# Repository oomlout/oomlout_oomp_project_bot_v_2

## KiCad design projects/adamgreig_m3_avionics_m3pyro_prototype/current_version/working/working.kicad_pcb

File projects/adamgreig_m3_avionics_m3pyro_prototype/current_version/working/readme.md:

# m3_avionics
 
## summary 
* id: adamgreig_m3_avionics_m3pyro_prototype
* user: adamgreig
* name: m3_avionics
* board: m3pyro_prototype
* repo: https://github.com/adamgreig/m3-avionics
* src_file_repo_kicad_pcb: m3pyro/firing_prototype/m3pyro_prototype.kicad_pcb
* src_file_repo_kicad_pcb_link: https://github.com/adamgreig/m3-avionics/tree/master/m3pyro/firing_prototype/m3pyro_prototype.kicad_pcb

* src_file_repo_sch: m3pyro/firing_prototype/m3pyro_prototype.sch
* src_file_repo_sch_link: https://github.com/adamgreig/m3-avionics/tree/master/m3pyro/firing_prototype/m3pyro_prototype.sch
* full details link: https://github.com/oomlout/oomlout_oomp_project_bot_v_2/tree/main/projects/adamgreig_m3_avionics_m3pyro_prototype/current_version/working  

## schematic  
  
[schematic (pdf)](working_schematic.pdf) 

## pcb  

[board (pdf)](working.pdf)  

## working_bom
| Id | Designator | Footprint | Quantity | Designation | Supplier and ref |  | None | 
| --- | --- | --- | --- | --- | --- | --- | --- | 
| 1 | L1 | XFL4020 | 1 | 2Âµ2 |  |  | [''] | 
| 2 | TP1 | TESTPAD | 1 | TESTPAD |  |  | [''] | 
| 3 | J1 | SIL-254P-02 | 1 | INPUT |  |  | [''] | 
| 4 | J2 | SIL-254P-02 | 1 | ENABLE |  |  | [''] | 
| 5 | J3 | SIL-254P-02 | 1 | OUTPUT |  |  | [''] | 
| 6 | IC1 | QFN-16-EP-TI | 1 | TPS62130 |  |  | [''] | 
| 7 | C1,C4 | 0603 | 2 | 10Âµ |  |  | [''] | 
| 8 | C2 | 0603 | 1 | 100n |  |  | [''] | 
| 9 | C3,R1,R2 | 0603 | 3 | DNP |  |  | [''] | 
| 10 | REF**,REF**,REF**,REF** | M3_MOUNT | 4 | M3_MOUNT |  |  | [''] | 

## bom_schematic
| Ref | Qnty | Value | Cmp name | Footprint | Description | Vendor | DNP | 
| --- | --- | --- | --- | --- | --- | --- | --- | 
| C1, C4 | 2 | 10Âµ | C | agg:0603 |  |  |  | 
| C2 | 1 | 100n | C | agg:0603 |  |  |  | 
| C3 | 1 | DNP | C | agg:0603 |  |  |  | 
| IC1 | 1 | TPS62130 | TPS62130 | agg:QFN-16-EP-TI |  |  |  | 
| J1 | 1 | INPUT | CONN_01x02 | agg:SIL-254P-02 |  |  |  | 
| J2 | 1 | ENABLE | CONN_01x02 | agg:SIL-254P-02 |  |  |  | 
| J3 | 1 | OUTPUT | CONN_01x02 | agg:SIL-254P-02 |  |  |  | 
| L1 | 1 | 2Âµ2 | L | agg:XFL4020 |  |  |  | 
| R1, R2 | 2 | DNP | R | agg:0603 |  |  |  | 
| TP1 | 1 | TESTPAD | TESTPAD | agg:TESTPAD |  |  |  |

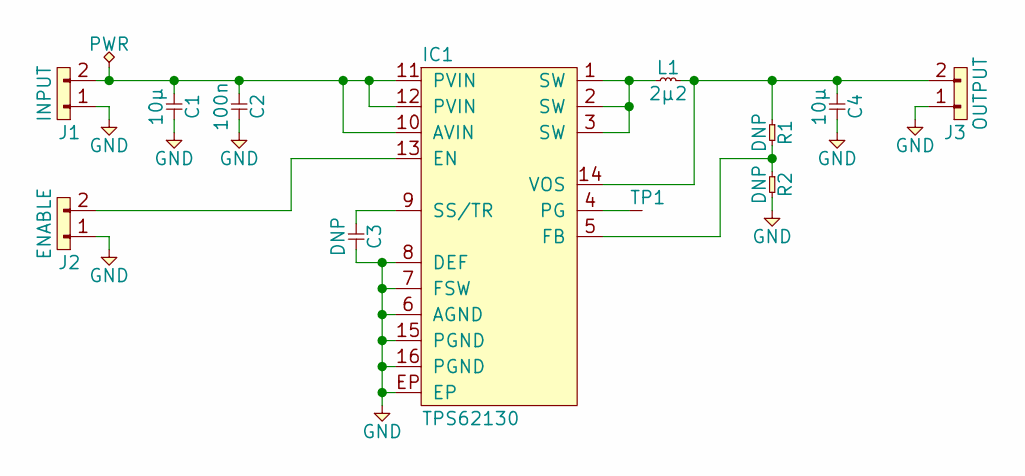
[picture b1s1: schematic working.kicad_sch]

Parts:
C1, C4: 10µ; 0603
C2: 100n; 0603
C3: DNP; 0603
IC1: TPS62130; QFN-16-EP-TI; Farnell 2361246
J1: INPUT; SIL-254P-02
J2: ENABLE; SIL-254P-02
J3: OUTPUT; SIL-254P-02
L1: 2µ2; XFL4020; Farnell 2289216
R1, R2: DNP; 0603
TP1: TESTPAD

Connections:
GND: C1.2, C2.2, C3.2, C4.2, IC1.6 (AGND), IC1.7 (FSW), IC1.8 (DEF), IC1.15 (PGND), IC1.16 (PGND), IC1.EP, J1.1, J2.1, J3.1, R2.2
unnamed: C1.1, C2.1, IC1.10 (AVIN), IC1.11 (PVIN), IC1.12 (PVIN), J1.2
unnamed: C3.1, IC1.9 (SS/TR)
unnamed: C4.1, IC1.14 (VOS), J3.2, L1.2, R1.1
unnamed: IC1.1 (SW), IC1.2 (SW), IC1.3 (SW), L1.1
unnamed: IC1.4 (PG), TP1.1
unnamed: IC1.5 (FB), R1.2, R2.1
unnamed: IC1.13 (EN), J2.2

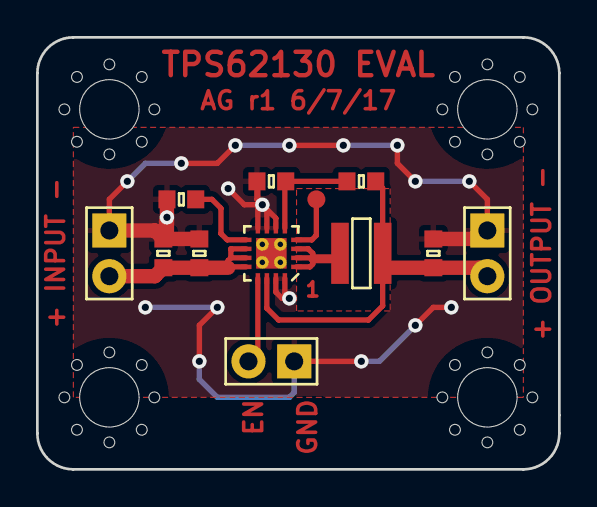
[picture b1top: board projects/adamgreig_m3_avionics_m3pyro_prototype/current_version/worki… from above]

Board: 2 copper layers, 29.0 x 24.0 mm, 12 parts (0 on the bottom side), 8 nets.

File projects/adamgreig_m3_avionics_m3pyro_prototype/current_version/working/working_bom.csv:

"Id";"Designator";"Footprint";"Quantity";"Designation";"Supplier and ref";
1;"L1";"XFL4020";1;"2µ2";;;
2;"TP1";"TESTPAD";1;"TESTPAD";;;
3;"J1";"SIL-254P-02";1;"INPUT";;;
4;"J2";"SIL-254P-02";1;"ENABLE";;;
5;"J3";"SIL-254P-02";1;"OUTPUT";;;
6;"IC1";"QFN-16-EP-TI";1;"TPS62130";;;
7;"C1,C4";"0603";2;"10µ";;;
8;"C2";"0603";1;"100n";;;
9;"C3,R1,R2";"0603";3;"DNP";;;
10;"REF**,REF**,REF**,REF**";"M3_MOUNT";4;"M3_MOUNT";;;

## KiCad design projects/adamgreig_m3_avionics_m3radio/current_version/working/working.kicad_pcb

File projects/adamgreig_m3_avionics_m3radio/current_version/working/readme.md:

# m3_avionics
 
## summary 
* id: adamgreig_m3_avionics_m3radio
* user: adamgreig
* name: m3_avionics
* board: m3radio
* repo: https://github.com/adamgreig/m3-avionics
* src_file_repo_kicad_pcb: m3radio/pcb_r2/m3radio.kicad_pcb
* src_file_repo_kicad_pcb_link: https://github.com/adamgreig/m3-avionics/tree/master/m3radio/pcb_r2/m3radio.kicad_pcb

* src_file_repo_sch: m3radio/gps-preamp/gps-preamp.sch
* src_file_repo_sch_link: https://github.com/adamgreig/m3-avionics/tree/master/m3radio/gps-preamp/gps-preamp.sch
* full details link: https://github.com/oomlout/oomlout_oomp_project_bot_v_2/tree/main/projects/adamgreig_m3_avionics_m3radio/current_version/working  

## schematic  
  
[schematic (pdf)](working_schematic.pdf) 

## pcb  

[board (pdf)](working.pdf)  

## working_bom
| Id | Designator | Footprint | Quantity | Designation | Supplier and ref |  | None | 
| --- | --- | --- | --- | --- | --- | --- | --- | 
| 1 | C103 | 0402 | 1 | 4u7 |  |  | [''] | 
| 2 | C104,C105,C107,C108,C109,C112,C113,C202,C1,C4,C9,C10 | 0402 | 12 | 100n |  |  | [''] | 
| 3 | C106,C2,C3,C7,C8 | 0402 | 5 | 1u |  |  | [''] | 
| 4 | C110,C111 | 0402 | 2 | 2u2 |  |  | [''] | 
| 5 | D101 | 0603-LED | 1 | RED |  |  | [''] | 
| 6 | D102 | 0603-LED | 1 | GRN |  |  | [''] | 
| 7 | IC101 | LQFP-64 | 1 | STM32F405RxTx |  |  | [''] | 
| 8 | IC102 | DFN-8-EP-MICROCHIP | 1 | MCP2562 |  |  | [''] | 
| 9 | IC201 | QFN-20-EP-SI | 1 | Si4461 |  |  | [''] | 
| 10 | J101 | TFML-110-02-L-D | 1 | WEST TOP |  |  | [''] | 
| 11 | J103 | TFML-110-02-L-D | 1 | EAST TOP |  |  | [''] | 
| 12 | R102,R103 | 0402 | 2 | 100 |  |  | [''] | 
| 13 | C201 | 0402 | 1 | 100p |  |  | [''] | 
| 14 | C203 | 0402 | 1 | 3p |  |  | [''] | 
| 15 | C204 | 0402 | 1 | 22p |  |  | [''] | 
| 16 | C205 | 0402 | 1 | 1p |  |  | [''] | 
| 17 | C206,C207 | 0402 | 2 | 5.6p |  |  | [''] | 
| 18 | L201 | 0603-L | 1 | 120nH |  |  | [''] | 
| 19 | L204 | 0603-L | 1 | 8.2nH |  |  | [''] | 
| 20 | C5,C11 | 0402 | 2 | 1n |  |  | [''] | 
| 21 | D1,D2 | 0402 | 2 | ESD_DIODE |  |  | [''] | 
| 22 | IC1 | DFN-6-EP-ONSEMI | 1 | NCP380 |  |  | [''] | 
| 23 | L1,L2,L3 | 0402-L | 3 | 91nH |  |  | [''] | 
| 24 | R1 | 0603 | 1 | 10 |  |  | [''] | 
| 25 | R2 | 0402 | 1 | 110k |  |  | [''] | 
| 26 | P101,P201 | U.FL-R-SMT-1 | 2 | COAX |  |  | [''] | 
| 27 | U1 | SC-70-5 | 1 | NCP4620 |  |  | [''] | 
| 28 | IC2 | SOT-23-5 | 1 | NC7SZ04 |  |  | [''] | 
| 29 | IC3 | MSOP-10 | 1 | CS2100-CP |  |  | [''] | 
| 30 | IC4 | DFN-10-SL18860DC | 1 | SL18860DC |  |  | [''] | 
| 31 | IC5 | MAX-M8Q | 1 | MAX_M8Q |  |  | [''] | 
| 32 | IC6 | SC-70-6 | 1 | SN74LVC1G0832 |  |  | [''] | 
| 33 | R3 | 0402 | 1 | 1M |  |  | [''] | 
| 34 | Y1 | TG-5006CG | 1 | TCXO |  |  | [''] | 
| 35 | C12 | 0402 | 1 | 220p |  |  | [''] | 
| 36 | L202 | 0402 | 1 | 20nH |  |  | [''] | 
| 37 | L203 | 0402 | 1 | 24nH |  |  | [''] | 
| 38 | L205 | 0402 | 1 | 6.8nH |  |  | [''] | 
| 39 | R4,R5 | 0402 | 2 | 10k |  |  | [''] | 
| 40 | C13 | 0402 | 1 | 2.2u |  |  | [''] | 
| 41 | J102 | SFML-110-02-L-D-LC | 1 | WEST BOT |  |  | [''] | 
| 42 | J104 | SFML-110-02-L-D-LC | 1 | EAST BOT |  |  | [''] | 

## bom_schematic
| Ref | Qnty | Value | Cmp name | Footprint | Description | Vendor | DNP | 
| --- | --- | --- | --- | --- | --- | --- | --- | 
| C1, C4, C9, C10, C104, C105, C107, C108, C109, C112, C113 | 11 | 100n | C | agg:0402 |  |  |  | 
| C2, C3, C7, C8, C106 | 5 | 1u | C | agg:0402 |  |  |  | 
| C5, C11 | 2 | 1n | C | agg:0402 |  |  |  | 
| C103 | 1 | 4u7 | C | agg:0402 |  |  |  | 
| C110, C111 | 2 | 2u2 | C | agg:0402 |  |  |  | 
| D1 | 1 | ESD_DIODE | ESD_DIODE | agg:0402 |  |  |  | 
| D101 | 1 | RED | LED | agg:0603-LED |  |  |  | 
| D102 | 1 | GRN | LED | agg:0603-LED |  |  |  | 
| IC1 | 1 | NCP380 | NCP380 | agg:DFN-6-EP-ONSEMI |  |  |  | 
| IC2 | 1 | NC7SZ04 | NC7SZ04 | agg:SOT-23-5 |  |  |  | 
| IC3 | 1 | CS2100-CP | CS2100-CP | agg:MSOP-10 |  |  |  | 
| IC4 | 1 | SL18860DC | SL18860DC | agg:DFN-10-SL18860DC |  |  |  | 
| IC5 | 1 | MAX_M8Q | MAX_M8Q | agg:MAX-M8Q |  |  |  | 
| IC6 | 1 | SN74LVC1G0832 | SN74LVC1G0832 | agg:SC-70-6 |  |  |  | 
| IC101 | 1 | STM32F405RxTx | STM32F405RxTx | agg:LQFP-64 |  |  |  | 
| IC102 | 1 | MCP2562 | MCP2562 | agg:DFN-8-EP-MICROCHIP |  |  |  | 
| J101 | 1 | WEST TOP | CONN_02x10 | agg:TFML-110-02-L-D |  |  |  | 
| J102 | 1 | WEST BOT | CONN_02x10 | agg:SFML-110-02-L-D-LC |  |  |  | 
| J103 | 1 | EAST TOP | CONN_02x10 | agg:TFML-110-02-L-D |  |  |  | 
| J104 | 1 | EAST BOT | CONN_02x10 | agg:SFML-110-02-L-D-LC |  |  |  | 
| L1, L2, L3 | 3 | 91nH | L | agg:0402-L |  |  |  | 
| P101 | 1 | COAX | COAX | M3radio:U.FL-R-SMT-1 |  |  |  | 
| R1 | 1 | 10 | R | agg:0603 |  |  |  | 
| R2 | 1 | 110k | R | agg:0402 |  |  |  | 
| R3 | 1 | 1M | R | agg:0402 |  |  |  | 
| R102, R103 | 2 | 100 | R | agg:0402 |  |  |  | 
| U1 | 1 | NCP4620 | NCP4620 | agg:SC-70-5 |  |  |  | 
| Y1 | 1 | TCXO | TCXO | agg:TG-5006CG |  |  |  |

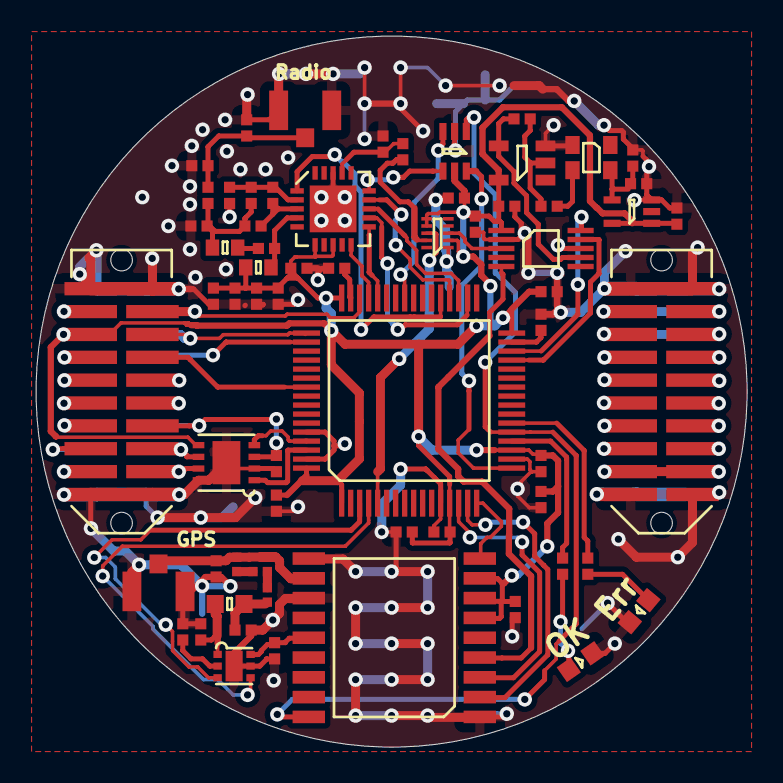
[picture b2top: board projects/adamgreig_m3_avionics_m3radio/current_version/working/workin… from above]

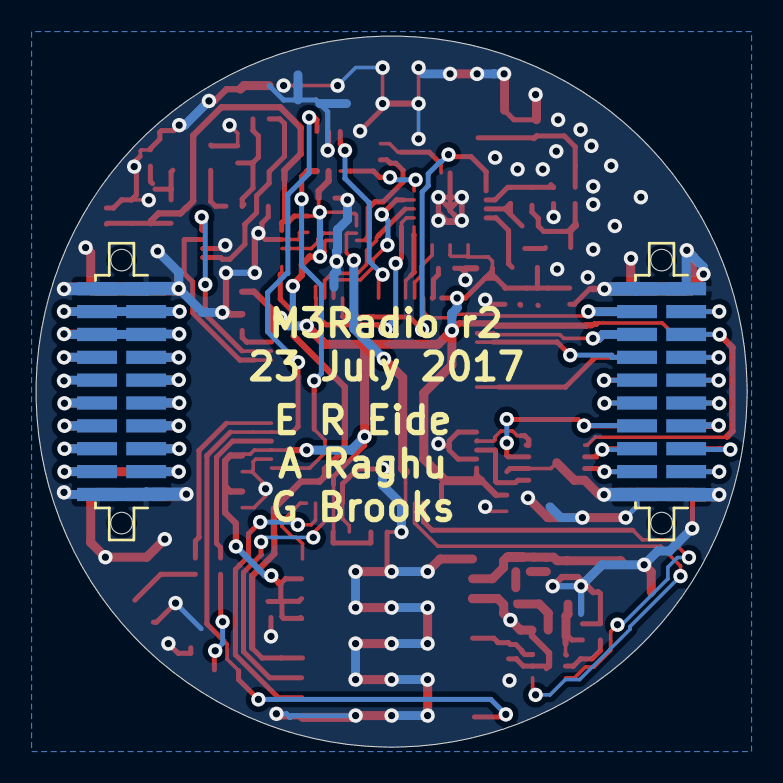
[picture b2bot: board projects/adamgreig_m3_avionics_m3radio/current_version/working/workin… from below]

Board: 2 copper layers, 39.5 x 39.5 mm, 66 parts (2 on the bottom side), 78 nets.

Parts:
C1, C4, C9, C10, C104, C105, C107, C108, C109, C112, C113, C202: 100n; 0402
C2, C3, C7, C8, C106: 1u; 0402
C5, C11: 1n; 0402
C12: 220p; 0402
C13: 2.2u; 0402
C103: 4u7; 0402
C110, C111: 2u2; 0402
C201: 100p; 0402
C203: 3p; 0402
C204: 22p; 0402
C205: 1p; 0402
C206, C207: 5.6p; 0402
D1, D2: ESD_DIODE; 0402
D101: RED; 0603-LED
D102: GRN; 0603-LED
IC1: NCP380; DFN-6-EP-ONSEMI
IC2: NC7SZ04; SOT-23-5
IC3: CS2100-CP; MSOP-10
IC4: SL18860DC; DFN-10-SL18860DC
IC5: MAX_M8Q; MAX-M8Q
IC6: SN74LVC1G0832; SC-70-6
IC101: STM32F405RxTx; LQFP-64
IC102: MCP2562; DFN-8-EP-MICROCHIP
IC201: Si4461; QFN-20-EP-SI
J101: WEST TOP; TFML-110-02-L-D
J102: WEST BOT; SFML-110-02-L-D-LC
J103: EAST TOP; TFML-110-02-L-D
J104: EAST BOT; SFML-110-02-L-D-LC
L1, L2, L3: 91nH; 0402-L
L201: 120nH; 0603-L
L202: 20nH; 0402
L203: 24nH; 0402
L204: 8.2nH; 0603-L
L205: 6.8nH; 0402
P101, P201: COAX; U.FL-R-SMT-1
R1: 10; 0603
R2: 110k; 0402
R3: 1M; 0402
R4, R5: 10k; 0402
R102, R103: 100; 0402
U1: NCP4620; SC-70-5
Y1: TCXO; TG-5006CG

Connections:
1v8: C4.1, C8.2, U1.4, Y1.4
3v3: C7.2, C9.1, C10.1, C11.2, C12.1, C13.1, C103.2, C104.2, C105.2, C106.2, C107.2, C108.2, C109.2, C113.1, C201.1, C202.1, IC2.5, IC3.1, IC4.2, IC4.6, IC4.7, IC5.6, IC5.7, IC5.8, IC6.5, IC101.1, IC101.13, IC101.19, IC101.32, IC101.48, IC101.64, IC102.5, IC201.6, IC201.8, J101.5, J102.5, L201.1, U1.1, U1.5
/3v3_AUX1: J101.13, J102.13
/3v3_AUX2: J101.15, J102.15
/3v3_DL: J101.11, J102.11
/3v3_FC: J101.7, J102.7
/3v3_IMU: J101.3, J102.3
/3v3_PYRO: J101.9, J102.9
/5v_AUX1: J103.11, J104.11
/5v_AUX2: J103.13, J104.13
/5v_CAM: J103.15, J104.15
/5v_CAN: C112.1, IC102.3, J101.14, J102.14
/5v_IMU: J103.9, J104.9
/5v_RADIO: J103.7, J104.7
/ANT_~EN: IC1.4, IC101.4
/ANT_~FLAG: IC1.3, IC101.3
/CAN+: IC102.7, J101.18, J102.18
/CAN-: IC102.6, J101.16, J102.16
/CAN_RXD: IC101.61, IC102.4
/CAN_TXD: IC101.62, IC102.1
/CHARGE: J103.17, J103.18, J104.17, J104.18
/GPS_PPS: IC5.18, IC6.1, IC101.21
/GPS_RESET_N: IC5.9, IC101.16
/GPS_RX: IC5.3, IC101.14
/GPS_TIM1: IC3.5, IC5.4
/GPS_TX: IC5.2, IC101.15
/JTCK: IC101.49, J101.6, J102.6
/JTDI: IC101.50, J102.8
/JTDO: IC101.55, J101.8
/JTDR: J101.10, J102.10
/JTMS: IC101.46, J101.4, J102.4
/LED_GRN: IC101.20, R103.1
/LED_RED: IC101.22, R102.1
/PLL_SCL: IC3.9, IC101.29
/PLL_SDA: IC3.10, IC101.30
/PWR: J103.16, J104.16
/PYRO1: J103.8, J104.8
/PYRO2: J103.10, J104.10
/PYRO3: J103.12, J104.12
/PYRO4: J103.14, J104.14
/PYRO_SI: J103.5, J103.6, J104.5, J104.6
/PYRO_SO: J103.3, J103.4, J104.3, J104.4
/RSVD1: J101.12, J102.12
/RSVD2: J101.17, J102.17
/Radio/RXn: C205.1, IC201.3, L202.1
/Radio/RXp: C203.1, IC201.2, L202.2, L203.1
/Radio/Radio_nSEL: IC6.4, IC201.15
/Radio/TX_pin: C204.1, IC201.4, L201.2
/Radio_CLK: IC4.9, R4.1
/Radio_GATE: IC6.3, IC101.41
/Radio_GPIO1: IC101.45, IC201.10
/Radio_SCLK: IC101.34, IC201.12
/Radio_SDI: IC101.36, IC201.14
/Radio_SDN: IC101.37, IC201.1
/Radio_SDO: IC101.35, IC201.13
/Radio_nIRQ: IC101.44, IC201.11
/Radio_nSEL: IC6.6, IC101.17
/STM_HSE: IC4.8, IC101.5
GND: C1.1, C2.2, C3.1, C4.2, C7.1, C8.1, C9.2, C10.2, C11.1, C12.2, C13.2, C103.1, C104.1, C105.1, C106.1, C107.1, C108.1, C109.1, C110.2, C111.2, C112.2, C113.2, C201.2, C202.2, C203.2, C206.2, C207.2, D1.2, D2.2, D101.1, D102.1, IC1.5, IC1.EP, IC2.3, IC3.2, IC3.8, IC4.1, IC5.1, IC5.10, IC5.12, IC6.2, IC101.12, IC101.18, IC101.60, IC101.63, IC102.2, IC102.8, IC102.EP, IC201.18, IC201.EP, J101.1, J101.2, J101.19, J101.20, J102.1, J102.2, J102.19, J102.20, J103.1, J103.2, J103.19, J103.20, J104.1, J104.2, J104.19, J104.20, P101.2, P201.2, R2.1, R5.2, U1.3, Y1.2
unnamed: C1.2, L3.1, R1.2
unnamed: C2.1, IC1.6, IC5.14
unnamed: C3.2, IC1.1, R1.1
unnamed: C5.1, IC2.2, R3.1
unnamed: C5.2, Y1.3
unnamed: C110.1, IC101.47
unnamed: C111.1, IC101.31
unnamed: C204.2, L204.1
unnamed: C205.2, C206.1, L203.2, L204.2, L205.1
unnamed: C207.1, D2.1, L205.2, P201.1
unnamed: D1.1, IC5.11, L1.2, P101.1
unnamed: D101.2, R102.2
unnamed: D102.2, R103.2
unnamed: IC1.2, R2.2
unnamed: IC2.4, IC3.7, R3.2
unnamed: IC3.3, IC4.3
unnamed: IC201.17, R4.2, R5.1
unnamed: L1.1, L2.2
unnamed: L2.1, L3.2

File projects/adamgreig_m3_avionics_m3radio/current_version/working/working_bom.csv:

"Id";"Designator";"Footprint";"Quantity";"Designation";"Supplier and ref";
1;"C103";"0402";1;"4u7";;;
2;"C104,C105,C107,C108,C109,C112,C113,C202,C1,C4,C9,C10";"0402";12;"100n";;;
3;"C106,C2,C3,C7,C8";"0402";5;"1u";;;
4;"C110,C111";"0402";2;"2u2";;;
5;"D101";"0603-LED";1;"RED";;;
6;"D102";"0603-LED";1;"GRN";;;
7;"IC101";"LQFP-64";1;"STM32F405RxTx";;;
8;"IC102";"DFN-8-EP-MICROCHIP";1;"MCP2562";;;
9;"IC201";"QFN-20-EP-SI";1;"Si4461";;;
10;"J101";"TFML-110-02-L-D";1;"WEST TOP";;;
11;"J103";"TFML-110-02-L-D";1;"EAST TOP";;;
12;"R102,R103";"0402";2;"100";;;
13;"C201";"0402";1;"100p";;;
14;"C203";"0402";1;"3p";;;
15;"C204";"0402";1;"22p";;;
16;"C205";"0402";1;"1p";;;
17;"C206,C207";"0402";2;"5.6p";;;
18;"L201";"0603-L";1;"120nH";;;
19;"L204";"0603-L";1;"8.2nH";;;
20;"C5,C11";"0402";2;"1n";;;
21;"D1,D2";"0402";2;"ESD_DIODE";;;
22;"IC1";"DFN-6-EP-ONSEMI";1;"NCP380";;;
23;"L1,L2,L3";"0402-L";3;"91nH";;;
24;"R1";"0603";1;"10";;;
25;"R2";"0402";1;"110k";;;
26;"P101,P201";"U.FL-R-SMT-1";2;"COAX";;;
27;"U1";"SC-70-5";1;"NCP4620";;;
28;"IC2";"SOT-23-5";1;"NC7SZ04";;;
29;"IC3";"MSOP-10";1;"CS2100-CP";;;
30;"IC4";"DFN-10-SL18860DC";1;"SL18860DC";;;
31;"IC5";"MAX-M8Q";1;"MAX_M8Q";;;
32;"IC6";"SC-70-6";1;"SN74LVC1G0832";;;
33;"R3";"0402";1;"1M";;;
34;"Y1";"TG-5006CG";1;"TCXO";;;
35;"C12";"0402";1;"220p";;;
36;"L202";"0402";1;"20nH";;;
37;"L203";"0402";1;"24nH";;;
38;"L205";"0402";1;"6.8nH";;;
39;"R4,R5";"0402";2;"10k";;;
40;"C13";"0402";1;"2.2u";;;
41;"J102";"SFML-110-02-L-D-LC";1;"WEST BOT";;;
42;"J104";"SFML-110-02-L-D-LC";1;"EAST BOT";;;

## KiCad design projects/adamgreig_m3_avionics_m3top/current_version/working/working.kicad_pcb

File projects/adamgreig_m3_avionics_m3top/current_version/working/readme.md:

# m3_avionics
 
## summary 
* id: adamgreig_m3_avionics_m3top
* user: adamgreig
* name: m3_avionics
* board: m3top
* repo: https://github.com/adamgreig/m3-avionics
* src_file_repo_kicad_pcb: m3top/m3top.kicad_pcb
* src_file_repo_kicad_pcb_link: https://github.com/adamgreig/m3-avionics/tree/master/m3top/m3top.kicad_pcb

* src_file_repo_sch: m3top/m3top.sch
* src_file_repo_sch_link: https://github.com/adamgreig/m3-avionics/tree/master/m3top/m3top.sch
* full details link: https://github.com/oomlout/oomlout_oomp_project_bot_v_2/tree/main/projects/adamgreig_m3_avionics_m3top/current_version/working  

## schematic  
  
[schematic (pdf)](working_schematic.pdf) 

## pcb  

[board (pdf)](working.pdf)  

## working_bom
| Id | Designator | Footprint | Quantity | Designation | Supplier and ref |  | None | 
| --- | --- | --- | --- | --- | --- | --- | --- | 
| 1 | J1 | B02B-PASK | 1 | PYRO5 |  |  | [''] | 
| 2 | J3 | B02B-PASK | 1 | PYRO6 |  |  | [''] | 
| 3 | J5 | B02B-PASK | 1 | PYRO7 |  |  | [''] | 
| 4 | J6 | B02B-PASK | 1 | PYRO8 |  |  | [''] | 
| 5 | J7 | B02B-PASK | 1 | 5v_CAM |  |  | [''] | 
| 6 | J8 | B02B-PASK | 1 | ARM |  |  | [''] | 
| 7 | J9 | B02B-PASK | 1 | PWR |  |  | [''] | 
| 8 | J10 | B02B-PASK | 1 | CHARGE |  |  | [''] | 
| 9 | J2 | SFML-110-02-L-D-LC | 1 | WEST BOT |  |  | [''] | 
| 10 | J4 | SFML-110-02-L-D-LC | 1 | EAST BOT |  |  | [''] | 
| 11 | D1,D2,D3,D4,D5,D9,D8,D7,D6 | 0402 | 9 | ESD_DIODE |  |  | [''] | 
| 12 | R1 | 0603 | 1 | 120 |  |  | [''] | 
| 13 | G*** | cusf_logo_small | 1 | LOGO |  |  | [''] | 

## bom_schematic
| Ref | Qnty | Value | Cmp name | Footprint | Description | Vendor | DNP | 
| --- | --- | --- | --- | --- | --- | --- | --- | 
| D1, D2, D3, D4, D5, D6, D7, D8, D9 | 9 | ESD_DIODE | ESD_DIODE | agg:0402 |  |  |  | 
| J1 | 1 | PYRO5 | CONN_01x02 | agg:B02B-PASK |  |  |  | 
| J2 | 1 | WEST BOT | CONN_02x10 | agg:SFML-110-02-L-D-LC |  |  |  | 
| J3 | 1 | PYRO6 | CONN_01x02 | agg:B02B-PASK |  |  |  | 
| J4 | 1 | EAST BOT | CONN_02x10 | agg:SFML-110-02-L-D-LC |  |  |  | 
| J5 | 1 | PYRO7 | CONN_01x02 | agg:B02B-PASK |  |  |  | 
| J6 | 1 | PYRO8 | CONN_01x02 | agg:B02B-PASK |  |  |  | 
| J7 | 1 | 5v_CAM | CONN_01x02 | agg:B02B-PASK |  |  |  | 
| J8 | 1 | ARM | CONN_01x02 | agg:B02B-PASK |  |  |  | 
| J9 | 1 | PWR | CONN_01x02 | agg:B02B-PASK |  |  |  | 
| J10 | 1 | CHARGE | CONN_01x02 | agg:B02B-PASK |  |  |  | 
| R1 | 1 | 120 | R | agg:0603 |  |  |  |

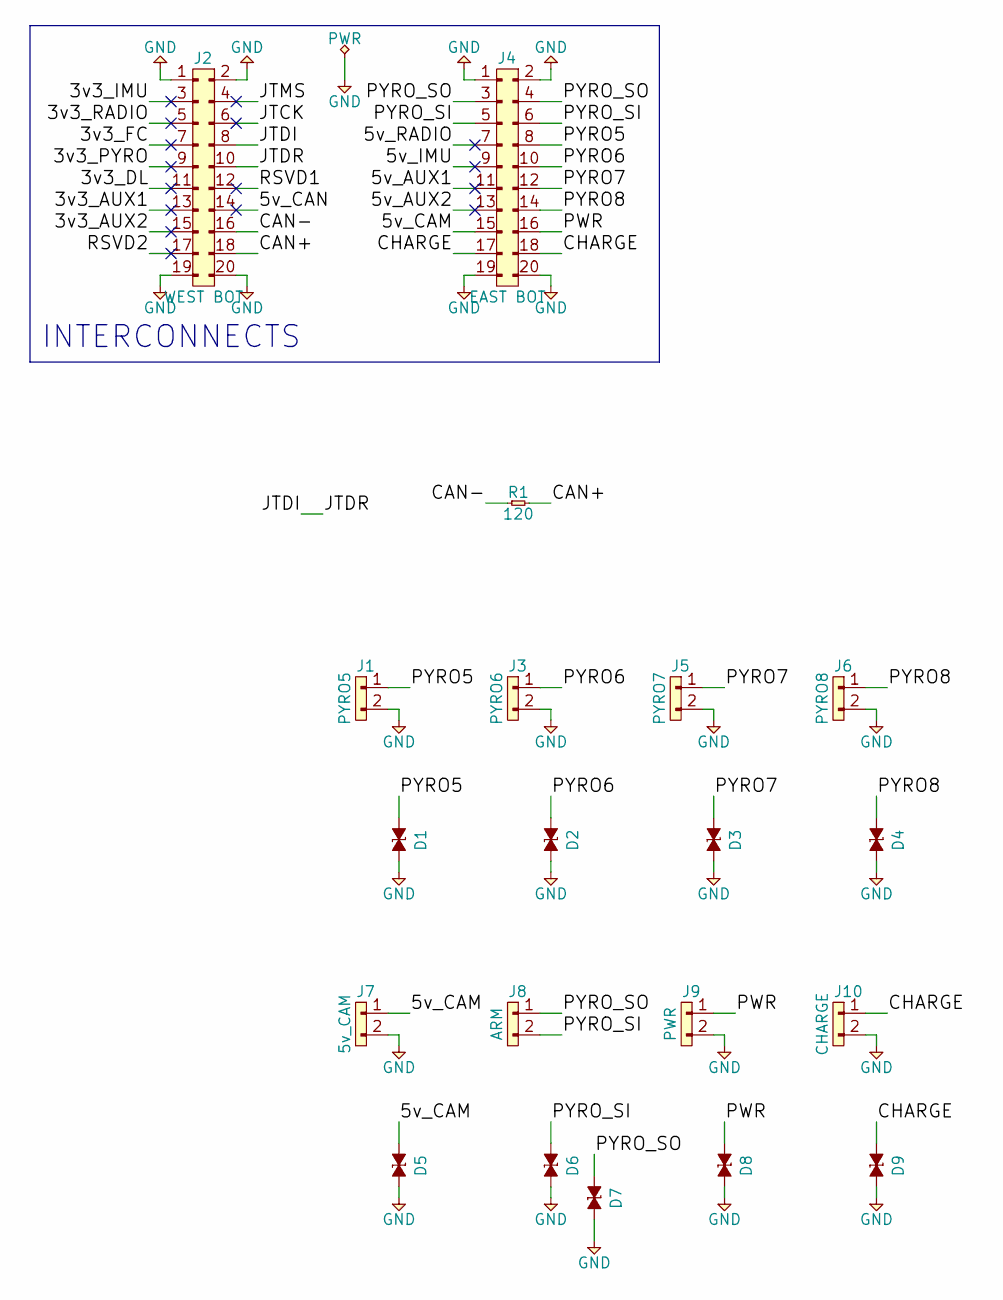
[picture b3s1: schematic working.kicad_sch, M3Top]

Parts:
D1, D2, D3, D4, D5, D6, D7, D8, D9: ESD_DIODE; 0402; Farnell 2368169
J1: PYRO5; B02B-PASK; Farnell 1830734
J2: WEST BOT; SFML-110-02-L-D-LC
J3: PYRO6; B02B-PASK; Farnell 1830734
J4: EAST BOT; SFML-110-02-L-D-LC
J5: PYRO7; B02B-PASK; Farnell 1830734
J6: PYRO8; B02B-PASK; Farnell 1830734
J7: 5v_CAM; B02B-PASK; Farnell 1830734
J8: ARM; B02B-PASK; Farnell 1830734
J9: PWR; B02B-PASK; Farnell 1830734
J10: CHARGE; B02B-PASK; Farnell 1830734
R1: 120; 0603; Farnell 9238379

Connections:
/3v3_AUX1: J2.13
/3v3_AUX2: J2.15
/3v3_DL: J2.11
/3v3_FC: J2.7
/3v3_IMU: J2.3
/3v3_PYRO: J2.9
/3v3_RADIO: J2.5
/5v_AUX1: J4.11
/5v_AUX2: J4.13
/5v_CAM: D5.1, J4.15, J7.1
/5v_CAN: J2.14
/5v_IMU: J4.9
/5v_RADIO: J4.7
/CAN+: J2.18, R1.2
/CAN-: J2.16, R1.1
/CHARGE: D9.1, J4.17, J4.18, J10.1
/JTCK: J2.6
/JTDI: J2.8, J2.10
/JTMS: J2.4
/PWR: D8.1, J4.16, J9.1
/PYRO5: D1.1, J1.1, J4.8
/PYRO6: D2.1, J3.1, J4.10
/PYRO7: D3.1, J4.12, J5.1
/PYRO8: D4.1, J4.14, J6.1
/PYRO_SI: D6.1, J4.5, J4.6, J8.2
/PYRO_SO: D7.1, J4.3, J4.4, J8.1
/RSVD1: J2.12
/RSVD2: J2.17
GND: D1.2, D2.2, D3.2, D4.2, D5.2, D6.2, D7.2, D8.2, D9.2, J1.2, J2.1, J2.2, J2.19, J2.20, J3.2, J4.1, J4.2, J4.19, J4.20, J5.2, J6.2, J7.2, J9.2, J10.2

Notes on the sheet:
INTERCONNECTS

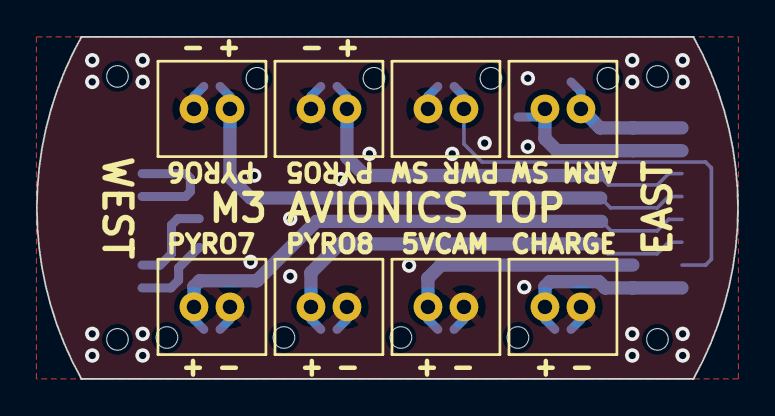
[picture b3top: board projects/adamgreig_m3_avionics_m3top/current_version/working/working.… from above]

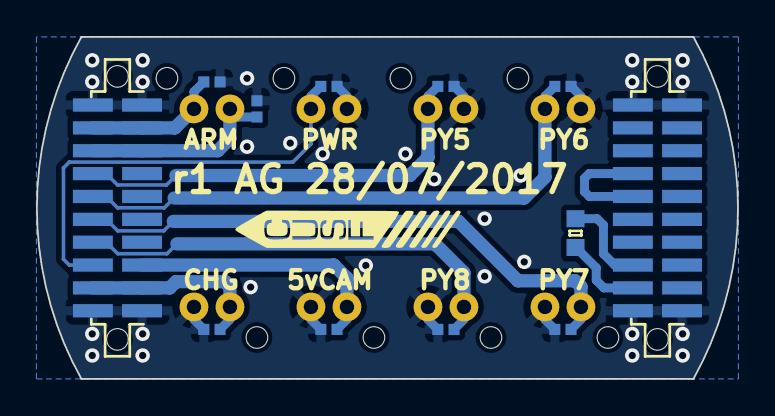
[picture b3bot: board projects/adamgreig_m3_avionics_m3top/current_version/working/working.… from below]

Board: 2 copper layers, 38.9 x 19.0 mm, 20 parts (12 on the bottom side), 13 nets.

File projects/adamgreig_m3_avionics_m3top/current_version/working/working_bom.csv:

"Id";"Designator";"Footprint";"Quantity";"Designation";"Supplier and ref";
1;"J1";"B02B-PASK";1;"PYRO5";;;
2;"J3";"B02B-PASK";1;"PYRO6";;;
3;"J5";"B02B-PASK";1;"PYRO7";;;
4;"J6";"B02B-PASK";1;"PYRO8";;;
5;"J7";"B02B-PASK";1;"5v_CAM";;;
6;"J8";"B02B-PASK";1;"ARM";;;
7;"J9";"B02B-PASK";1;"PWR";;;
8;"J10";"B02B-PASK";1;"CHARGE";;;
9;"J2";"SFML-110-02-L-D-LC";1;"WEST BOT";;;
10;"J4";"SFML-110-02-L-D-LC";1;"EAST BOT";;;
11;"D1,D2,D3,D4,D5,D9,D8,D7,D6";"0402";9;"ESD_DIODE";;;
12;"R1";"0603";1;"120";;;
13;"G***";"cusf_logo_small";1;"LOGO";;;

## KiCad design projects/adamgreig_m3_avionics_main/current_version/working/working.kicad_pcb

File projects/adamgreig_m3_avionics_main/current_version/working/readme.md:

# m3_avionics
 
## summary 
* id: adamgreig_m3_avionics_main
* user: adamgreig
* name: m3_avionics
* board: main
* repo: https://github.com/adamgreig/m3-avionics
* src_file_repo_kicad_pcb: m3dl/main/main.kicad_pcb
* src_file_repo_kicad_pcb_link: https://github.com/adamgreig/m3-avionics/tree/master/m3dl/main/main.kicad_pcb

* src_file_repo_sch: m3dl/main/main.sch
* src_file_repo_sch_link: https://github.com/adamgreig/m3-avionics/tree/master/m3dl/main/main.sch
* full details link: https://github.com/oomlout/oomlout_oomp_project_bot_v_2/tree/main/projects/adamgreig_m3_avionics_main/current_version/working  

## schematic  
  
[schematic (pdf)](working_schematic.pdf) 

## pcb  

[board (pdf)](working.pdf)  

## working_bom
| Id | Designator | Footprint | Quantity | Designation | Supplier and ref |  | None | 
| --- | --- | --- | --- | --- | --- | --- | --- | 
| 1 | C1,C6,C12,C13,C7,C8,C9,C14,C16 | 0603-L | 9 | 100n |  |  | [''] | 
| 2 | C2,C3 | 0603-L | 2 | 10p |  |  | [''] | 
| 3 | C4,C5 | 0603-L | 2 | 2u2 |  |  | [''] | 
| 4 | C10 | 0603-L | 1 | 4u7 |  |  | [''] | 
| 5 | IC1 | LQFP-64 | 1 | STM32F405RxTx |  |  | [''] | 
| 6 | IC2 | DFN-8-EP-MICROCHIP | 1 | MCP2562 |  |  | [''] | 
| 7 | J1 | TFML-110-02-L-D | 1 | WEST TOP |  |  | [''] | 
| 8 | J2 | TFML-110-02-L-D | 1 | EAST TOP |  |  | [''] | 
| 9 | P1 | TC2030-NL | 1 | SWD_TC |  |  | [''] | 
| 10 | R1,R4,R5,R6,R7 | 0603-L | 5 | 47K |  |  | [''] | 
| 11 | R2 | 0603-L | 1 | 100R |  |  | [''] | 
| 12 | Y1 | XTAL-20x16 | 1 | 26MHz |  |  | [''] | 
| 13 | R3,R9,R10,R8 | 0603-L | 4 | 1k |  |  | [''] | 
| 14 | J6 | Connector_Molex_PicoBlade_53261-0471 | 1 | USB |  |  | [''] | 
| 15 | G*** | cusf_logo_full | 1 | LOGO |  |  | [''] | 
| 16 | D1,D2,D3 | 0603-LED | 3 | LED |  |  | [''] | 
| 17 | C15 | 0603-L | 1 | 1u |  |  | [''] | 
| 18 | J3 | SFML-110-02-L-D-LC | 1 | WEST BOT |  |  | [''] | 
| 19 | J4 | SFML-110-02-L-D-LC | 1 | EAST BOT |  |  | [''] | 
| 20 | J7 | SFML-110-02-L-D-LC | 1 | SOUTH BOT |  |  | [''] | 
| 21 | U1 | MICROSD_MOLEX_503398-1892 | 1 | MICROSD |  |  | [''] | 

## bom_schematic
| Ref | Qnty | Value | Cmp name | Footprint | Description | Vendor | DNP | 
| --- | --- | --- | --- | --- | --- | --- | --- | 
| C1, C6, C7, C8, C9, C12, C13, C14, C16 | 9 | 100n | C_Small | Capacitors_SMD:C_0603 |  |  |  | 
| C2, C3 | 2 | 10p | C_Small | Capacitors_SMD:C_0603 |  |  |  | 
| C4, C5 | 2 | 2u2 | C_Small | Capacitors_SMD:C_0603 |  |  |  | 
| C10 | 1 | 4u7 | C_Small | Capacitors_SMD:C_0603 |  |  |  | 
| C15 | 1 | 1u | C_Small | Capacitors_SMD:C_0603 |  |  |  | 
| D1, D2, D3 | 3 | LED | LED | agg:0603-LED |  |  |  | 
| IC1 | 1 | STM32F405RxTx | STM32F405RxTx | agg:LQFP-64 |  |  |  | 
| IC2 | 1 | MCP2562 | MCP2562 | agg:DFN-8-EP-MICROCHIP |  |  |  | 
| J1 | 1 | WEST TOP | CONN_02x10 | agg:TFML-110-02-L-D |  |  |  | 
| J2 | 1 | EAST TOP | CONN_02x10 | agg:TFML-110-02-L-D |  |  |  | 
| J3 | 1 | WEST BOT | CONN_02x10 | agg:SFML-110-02-L-D-LC |  |  |  | 
| J4 | 1 | EAST BOT | CONN_02x10 | agg:SFML-110-02-L-D-LC |  |  |  | 
| J6 | 1 | USB | CONN_01x04 | Connectors_Molex:Connector_Molex_PicoBlade_53261-0471 |  |  |  | 
| J7 | 1 | SOUTH BOT | CONN_02x10 | agg:SFML-110-02-L-D-LC |  |  |  | 
| P1 | 1 | SWD_TC | SWD_TC | agg:TC2030-NL |  |  |  | 
| R1, R4, R5, R6, R7 | 5 | 47K | R | Resistors_SMD:R_0603 |  |  |  | 
| R2 | 1 | 100R | R | Resistors_SMD:R_0603 |  |  |  | 
| R3, R8, R9, R10 | 4 | 1k | R | agg:0603-L |  |  |  | 
| U1 | 1 | MICROSD | MICROSD-RESCUE-main | agg:MICROSD_MOLEX_503398-1892 |  |  |  | 
| Y1 | 1 | 26MHz | XTAL | agg:XTAL-20x16 |  |  |  |

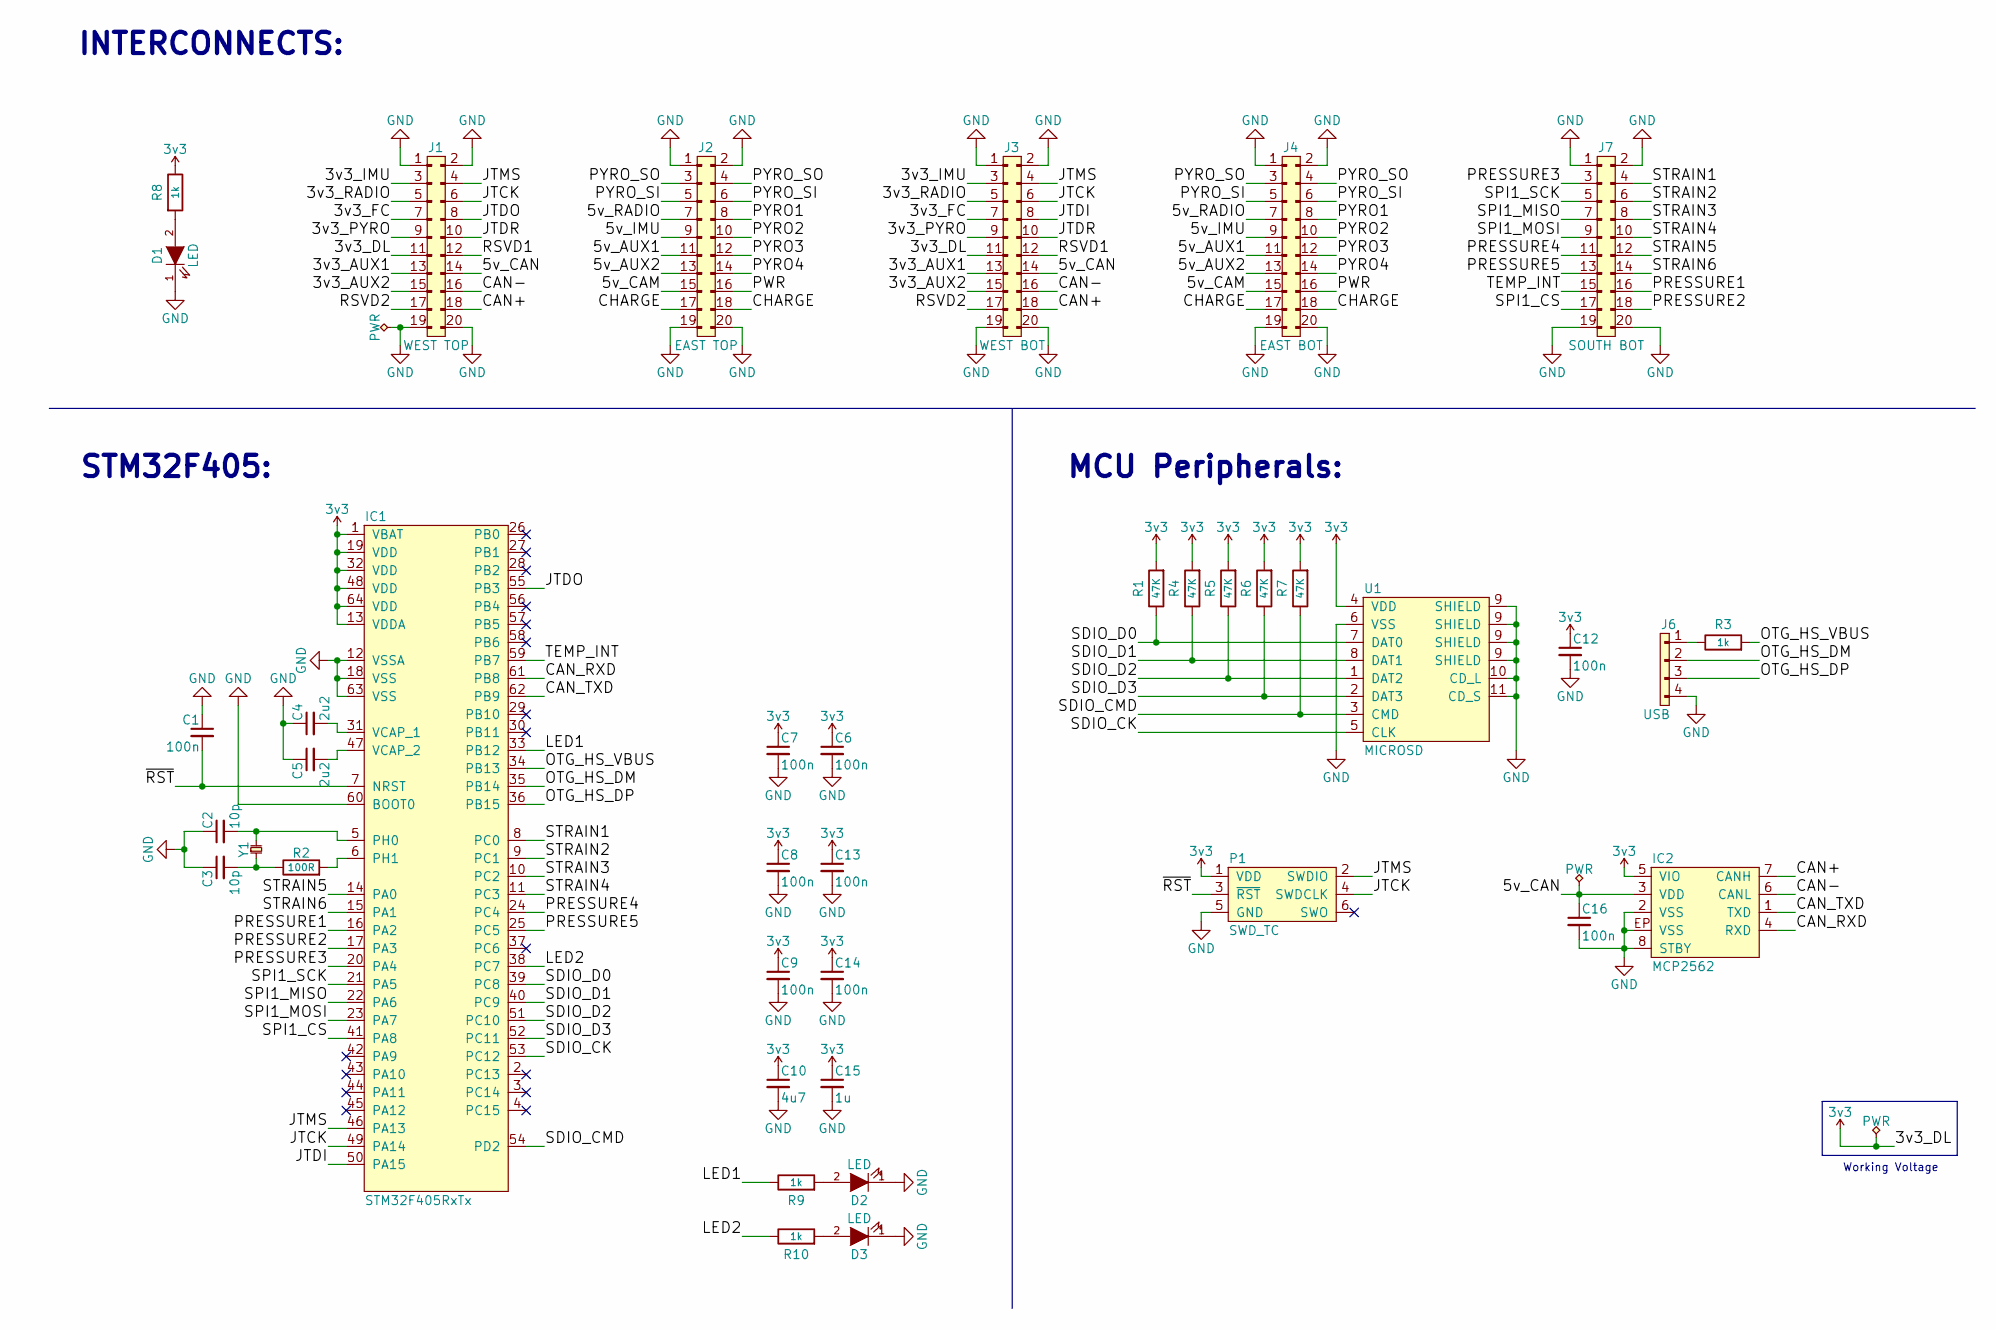
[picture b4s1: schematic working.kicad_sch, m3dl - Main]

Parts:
C1, C6, C7, C8, C9, C12, C13, C14, C16: 100n; C_0603; Farnell 2496834
C2, C3: 10p; C_0603; Farnell 2309035
C4, C5: 2u2; C_0603; Farnell 1797012
C10: 4u7; C_0603; Farnell 2496930
C15: 1u; C_0603; Farnell 1865556
D1, D2: LED; 0603-LED; Farnell 2290328
D3: LED; 0603-LED; Farnell 2290329
IC1: STM32F405RxTx; LQFP-64; Farnell 2064363
IC2: MCP2562; DFN-8-EP-MICROCHIP; Farnell 2448755
J1: WEST TOP; TFML-110-02-L-D
J2: EAST TOP; TFML-110-02-L-D
J3: WEST BOT; SFML-110-02-L-D-LC
J4: EAST BOT; SFML-110-02-L-D-LC
J6: USB; Connector_Molex_PicoBlade_53261-0471; Farnell 1125374
J7: SOUTH BOT; SFML-110-02-L-D-LC
P1: SWD_TC; TC2030-NL
R1, R4, R5, R6, R7: 47K; R_0603; Farnell 9238689
R2: 100R; R_0603; Farnell 2502395
R3, R8, R9, R10: 1k; 0603-L; Farnell 2309108
U1: MICROSD; MICROSD_MOLEX_503398-1892; Farnell 2358234
Y1: 26MHz; XTAL-20x16; Farnell 2506952

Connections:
3v3: C6.1, C7.1, C8.1, C9.1, C10.1, C12.1, C13.1, C14.1, C15.1, IC1.1 (VBAT), IC1.13 (VDDA), IC1.19 (VDD), IC1.32 (VDD), IC1.48 (VDD), IC1.64 (VDD), IC2.5 (VIO), J1.11, J3.11, P1.1 (VDD), R1.2, R4.2, R5.2, R6.2, R7.2, R8.1, U1.4 (VDD)
/3v3_AUX1: J1.13, J3.13
/3v3_AUX2: J1.15, J3.15
/3v3_FC: J1.7, J3.7
/3v3_IMU: J1.3, J3.3
/3v3_PYRO: J1.9, J3.9
/3v3_RADIO: J1.5, J3.5
/5v_AUX1: J2.11, J4.11
/5v_AUX2: J2.13, J4.13
/5v_CAM: J2.15, J4.15
/5v_CAN: C16.1, IC2.3 (VDD), J1.14, J3.14
/5v_IMU: J2.9, J4.9
/5v_RADIO: J2.7, J4.7
/CAN+: IC2.7 (CANH), J1.18, J3.18
/CAN-: IC2.6 (CANL), J1.16, J3.16
/CAN_RXD: IC1.61 (PB8), IC2.4 (RXD)
/CAN_TXD: IC1.62 (PB9), IC2.1 (TXD)
/CHARGE: J2.17, J2.18, J4.17, J4.18
/JTCK: IC1.49 (PA14), J1.6, J3.6, P1.4 (SWDCLK)
/JTDI: IC1.50 (PA15), J3.8
/JTDO: IC1.55 (PB3), J1.8
/JTDR: J1.10, J3.10
/JTMS: IC1.46 (PA13), J1.4, J3.4, P1.2 (SWDIO)
/LED1: IC1.33 (PB12), R9.1
/LED2: IC1.38 (PC7), R10.1
/OTG_HS_DM: IC1.35 (PB14), J6.2
/OTG_HS_DP: IC1.36 (PB15), J6.3
/OTG_HS_VBUS: IC1.34 (PB13), R3.2
/PRESSURE1: IC1.16 (PA2), J7.16
/PRESSURE2: IC1.17 (PA3), J7.18
/PRESSURE3: IC1.20 (PA4), J7.3
/PRESSURE4: IC1.24 (PC4), J7.11
/PRESSURE5: IC1.25 (PC5), J7.13
/PWR: J2.16, J4.16
/PYRO1: J2.8, J4.8
/PYRO2: J2.10, J4.10
/PYRO3: J2.12, J4.12
/PYRO4: J2.14, J4.14
/PYRO_SI: J2.5, J2.6, J4.5, J4.6
/PYRO_SO: J2.3, J2.4, J4.3, J4.4
/RSVD1: J1.12, J3.12
/RSVD2: J1.17, J3.17
/SDIO_CK: IC1.53 (PC12), U1.5 (CLK)
/SDIO_CMD: IC1.54 (PD2), R7.1, U1.3 (CMD)
/SDIO_D0: IC1.39 (PC8), R1.1, U1.7 (DAT0)
/SDIO_D1: IC1.40 (PC9), R4.1, U1.8 (DAT1)
/SDIO_D2: IC1.51 (PC10), R5.1, U1.1 (DAT2)
/SDIO_D3: IC1.52 (PC11), R6.1, U1.2 (DAT3)
/SPI1_CS: IC1.41 (PA8), J7.17
/SPI1_MISO: IC1.22 (PA6), J7.7
/SPI1_MOSI: IC1.23 (PA7), J7.9
/SPI1_SCK: IC1.21 (PA5), J7.5
/STRAIN1: IC1.8 (PC0), J7.4
/STRAIN2: IC1.9 (PC1), J7.6
/STRAIN3: IC1.10 (PC2), J7.8
/STRAIN4: IC1.11 (PC3), J7.10
/STRAIN5: IC1.14 (PA0), J7.12
/STRAIN6: IC1.15 (PA1), J7.14
/TEMP_INT: IC1.59 (PB7), J7.15
/~RST: C1.2, IC1.7 (NRST), P1.3 (~RST)
GND: C1.1, C2.1, C3.1, C4.1, C5.1, C6.2, C7.2, C8.2, C9.2, C10.2, C12.2, C13.2, C14.2, C15.2, C16.2, D1.1 (K), D2.1 (K), D3.1 (K), IC1.12 (VSSA), IC1.18 (VSS), IC1.60 (BOOT0), IC1.63 (VSS), IC2.2 (VSS), IC2.8 (STBY), IC2.EP (VSS), J1.1, J1.2, J1.19, J1.20, J2.1, J2.2, J2.19, J2.20, J3.1, J3.2, J3.19, J3.20, J4.1, J4.2, J4.19, J4.20, J6.4, J7.1, J7.2, J7.19, J7.20, P1.5 (GND), U1.6 (VSS), U1.9 (SHIELD), U1.10 (CD_L), U1.11 (CD_S)
unnamed: C2.2, IC1.5 (PH0), Y1.2
unnamed: C3.2, R2.1, Y1.1
unnamed: C4.2, IC1.31 (VCAP_1)
unnamed: C5.2, IC1.47 (VCAP_2)
unnamed: D1.2 (A), R8.2
unnamed: D2.2 (A), R9.2
unnamed: D3.2 (A), R10.2
unnamed: IC1.6 (PH1), R2.2
unnamed: J6.1, R3.1

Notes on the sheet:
STM32F405:
MCU Peripherals:
INTERCONNECTS:
Working Voltage

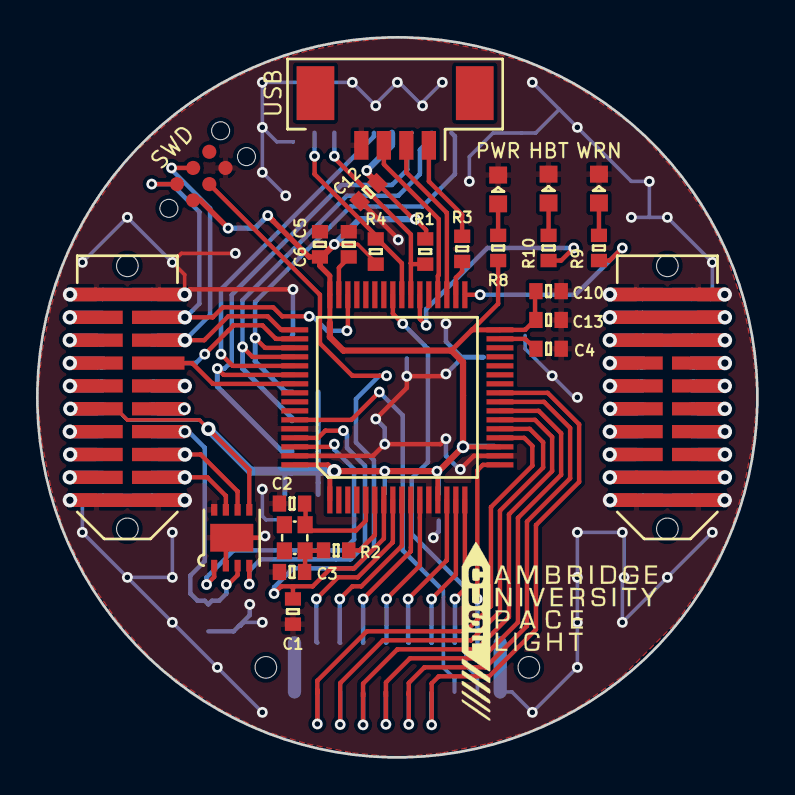
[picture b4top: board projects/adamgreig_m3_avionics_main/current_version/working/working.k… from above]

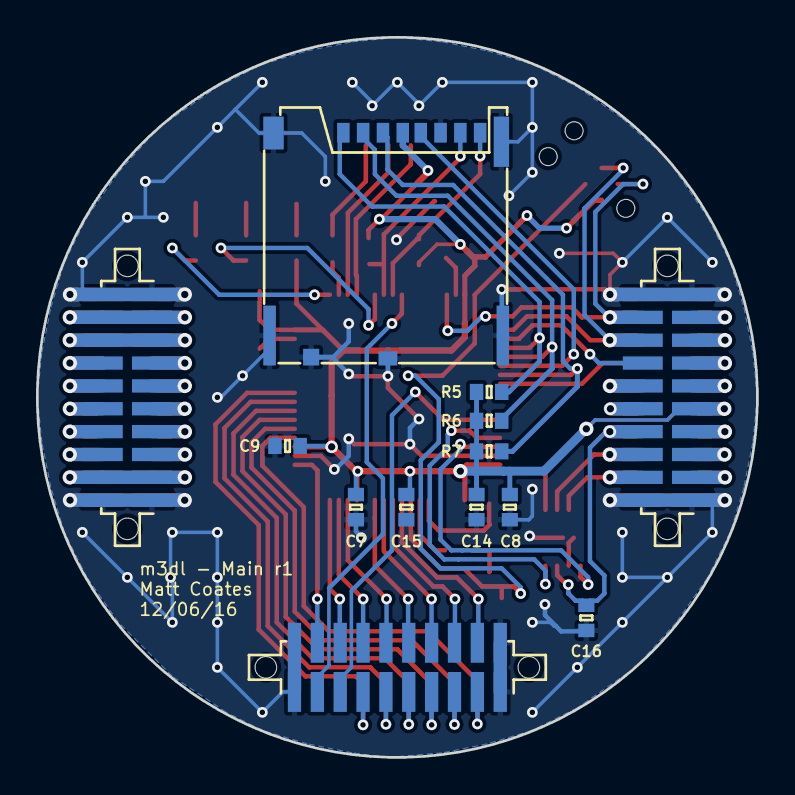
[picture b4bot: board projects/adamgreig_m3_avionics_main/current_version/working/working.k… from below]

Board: 2 copper layers, 40.0 x 40.0 mm, 39 parts (13 on the bottom side), 70 nets.

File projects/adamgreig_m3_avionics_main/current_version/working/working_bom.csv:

"Id";"Designator";"Footprint";"Quantity";"Designation";"Supplier and ref";
1;"C1,C6,C12,C13,C7,C8,C9,C14,C16";"0603-L";9;"100n";;;
2;"C2,C3";"0603-L";2;"10p";;;
3;"C4,C5";"0603-L";2;"2u2";;;
4;"C10";"0603-L";1;"4u7";;;
5;"IC1";"LQFP-64";1;"STM32F405RxTx";;;
6;"IC2";"DFN-8-EP-MICROCHIP";1;"MCP2562";;;
7;"J1";"TFML-110-02-L-D";1;"WEST TOP";;;
8;"J2";"TFML-110-02-L-D";1;"EAST TOP";;;
9;"P1";"TC2030-NL";1;"SWD_TC";;;
10;"R1,R4,R5,R6,R7";"0603-L";5;"47K";;;
11;"R2";"0603-L";1;"100R";;;
12;"Y1";"XTAL-20x16";1;"26MHz";;;
13;"R3,R9,R10,R8";"0603-L";4;"1k";;;
14;"J6";"Connector_Molex_PicoBlade_53261-0471";1;"USB";;;
15;"G***";"cusf_logo_full";1;"LOGO";;;
16;"D1,D2,D3";"0603-LED";3;"LED";;;
17;"C15";"0603-L";1;"1u";;;
18;"J3";"SFML-110-02-L-D-LC";1;"WEST BOT";;;
19;"J4";"SFML-110-02-L-D-LC";1;"EAST BOT";;;
20;"J7";"SFML-110-02-L-D-LC";1;"SOUTH BOT";;;
21;"U1";"MICROSD_MOLEX_503398-1892";1;"MICROSD";;;
